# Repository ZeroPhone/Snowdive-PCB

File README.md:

# Snowdive PCBs

- `top_board_zero`: Snowdive top board for Pi Zero-compatible SBCs
- `bottom_board_palmtop`: Snowdive addon board that converts a top board into a palmtop

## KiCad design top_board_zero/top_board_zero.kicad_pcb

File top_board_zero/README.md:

# TOP-PIZERO Snowdive board v0

This board is confirmed to function standalone. It also is designed (but currently untested) to function connected to a bottom board, for instance, the BTM-PALMTOP.

## Requirements

This board works from a 5V/1.5A or 5V/3A input. If you want to get USB host mode out of the, you can use many of the generic "USB-C with data output and charger input" docks; connect the charger first, then plug the USB-C into the board.

You can still use the Pi Zero HDMI port for setup if required for OS setup.

You might benefit from a USB-UART adapter for debugging the system, though it's not required. A USB-UART adapter can be connected into the expansion header. Remember to check config.txt and cmdline.txt to make sure that UART console is enabled.

## Assembly

### FIXES REQUIRED FOR V0

- Remove resistor R6 (next to I2C GPIO expander U27 in the section `I2C GPIO a`),
- Add a ~51K resistor soldered to the VSYS side of C51 in `modem buck` section (can reuse the removed R6 for this)m
- Magnet wire the added resistor's other pin to pin 6 (EN) of U17 MIC2876, signal `EN_5V_BOOST`, section `5V boost`,
- Remove neopixels LED1 and LED2 at the top of the board (unless you've ensured that they're assembled correctly by JLCPCB, which has a likelihood of 50%).
- Desolder the TVS diode D5 in the `LTE modem` section if it's found out to be shorting the modem VBAT `+3V5` rail (possible if it was assembled incorrectly by JLCPCB, which has a likelihood of 50%).

### After-PCBA steps

- If assembled without a modem, solder on a modem as desired (not required)
- If assembled single-sided, solder on a SIM slot and an expansion header as desired (not required)
- Solder the Pi Zero on flush onto the board. Use a headers-less Pi Zero.
- Solder the Pi Zero USB testpoints to the solder points under the board using thin wires (i.e. magnet wire or stranded wire). Check for shorts to GND (in particular the microUSB shield pads) after soldering.

### After-assembly preparations

None.

## Bringup

### Testing under Linux

Make sure to run raspi-config to enable I2C, and that `i2c-dev` is added into `/etc/modules`.

### USB subsystem

**Before attempting to work with data on the USB-C port, slide the switch right next to it away from the USB-C port. This will disengage the hardware switch on the USB data pins.**

By default, USB from the Pi Zero is routed directly to the USB-C socket. This allows you to use the USB gadget mode (for networking/serial/storage over USB), as well as the BCM bootloader mode (entered upon boot without an SD card inserted).

If you want to enable the onboard USB hub (including the modem USB downlink and two of the downlinks exposed to a bottom board), you have to run these console commands:

```bash
i2cset -y 1 0x24 7 0xaf; i2cset -y 1 0x24 3 0xef
```

The `i2c-tools` package is a prerequisite for this - you can get it by using `sudo apt install i2c-tools`.

The USB-C socket will then get connected through a USB hub, instead of being connected directly.

Note: This command can also be executed when using a network connection over USB (i.e. USB-Ethernet), but do expect that you might need to open a new SSH session, as the old session might freeze.

*Next revision will join these pins into a single GPIO, so the command for V1 will change.*

### Modem

To power up the modem `+3V5` power rail, issue this command:

```bash
i2cset -y 1 0x25 7 0xef
```

The `i2c-tools` package is a prerequisite for this - you can get it by using `sudo apt install i2c-tools`.

## Notes

- I recommend ordering PCBA (PCB with assembly) for this board.
- The board is prepared for PCBA ordering, use the [kicad-jlcpcb-tools](https://github.com/Bouni/kicad-jlcpcb-tools/) plugin to generate output files.
- I recommend a stencil for assembling this board.

## Info

- Software: Kicad 9
- Version: 0
- PCB size: 111x80
- Layer count: 2
- Recommended thickness: 1.6mm

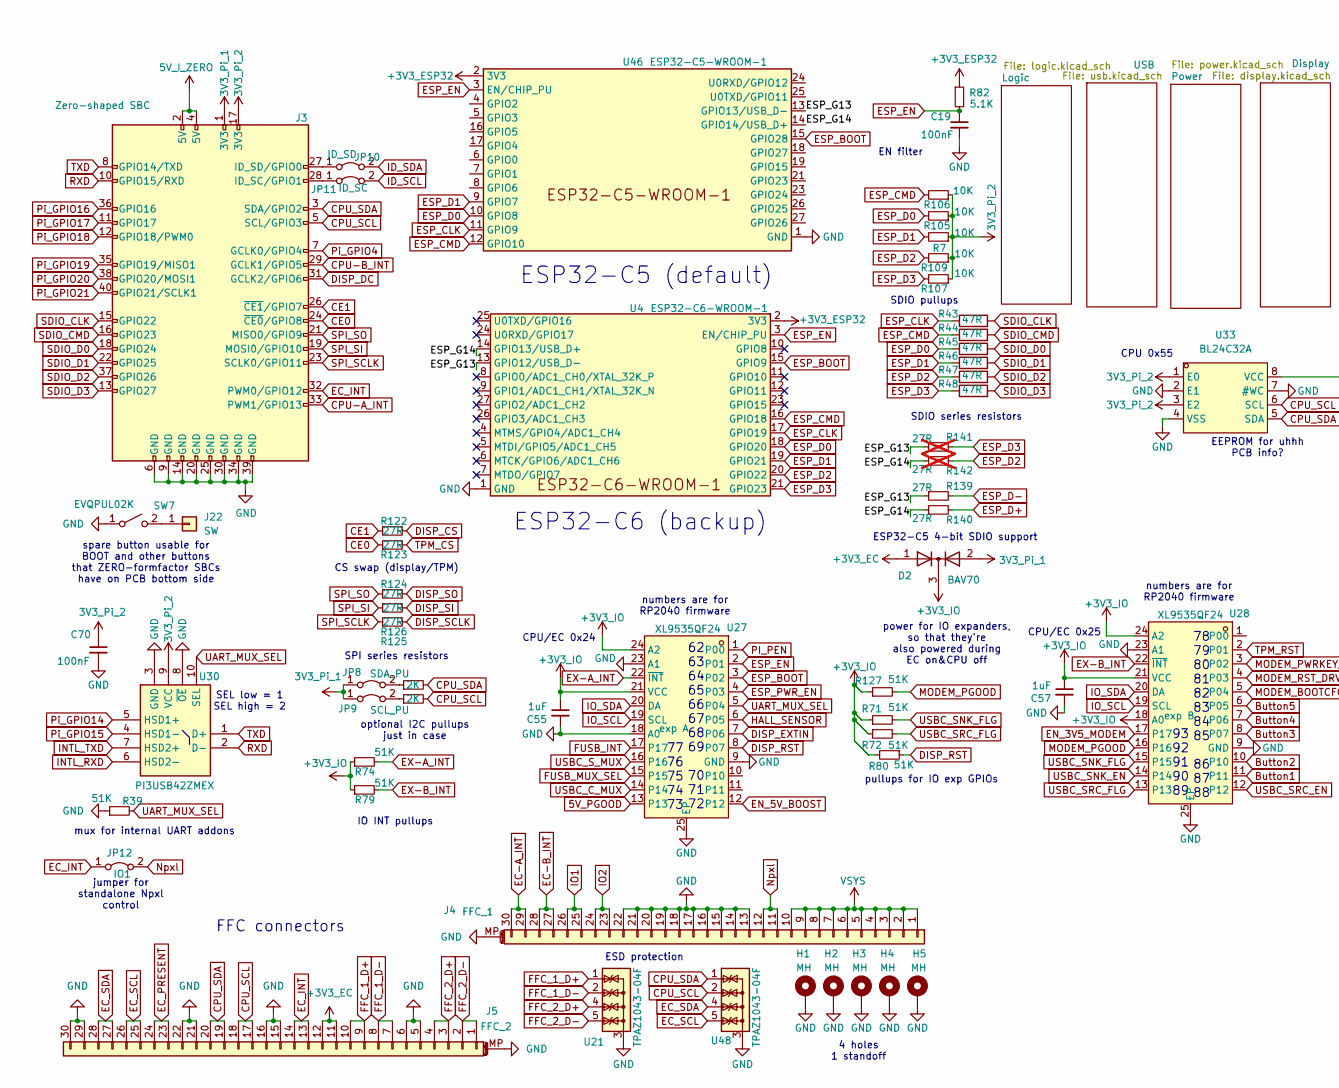
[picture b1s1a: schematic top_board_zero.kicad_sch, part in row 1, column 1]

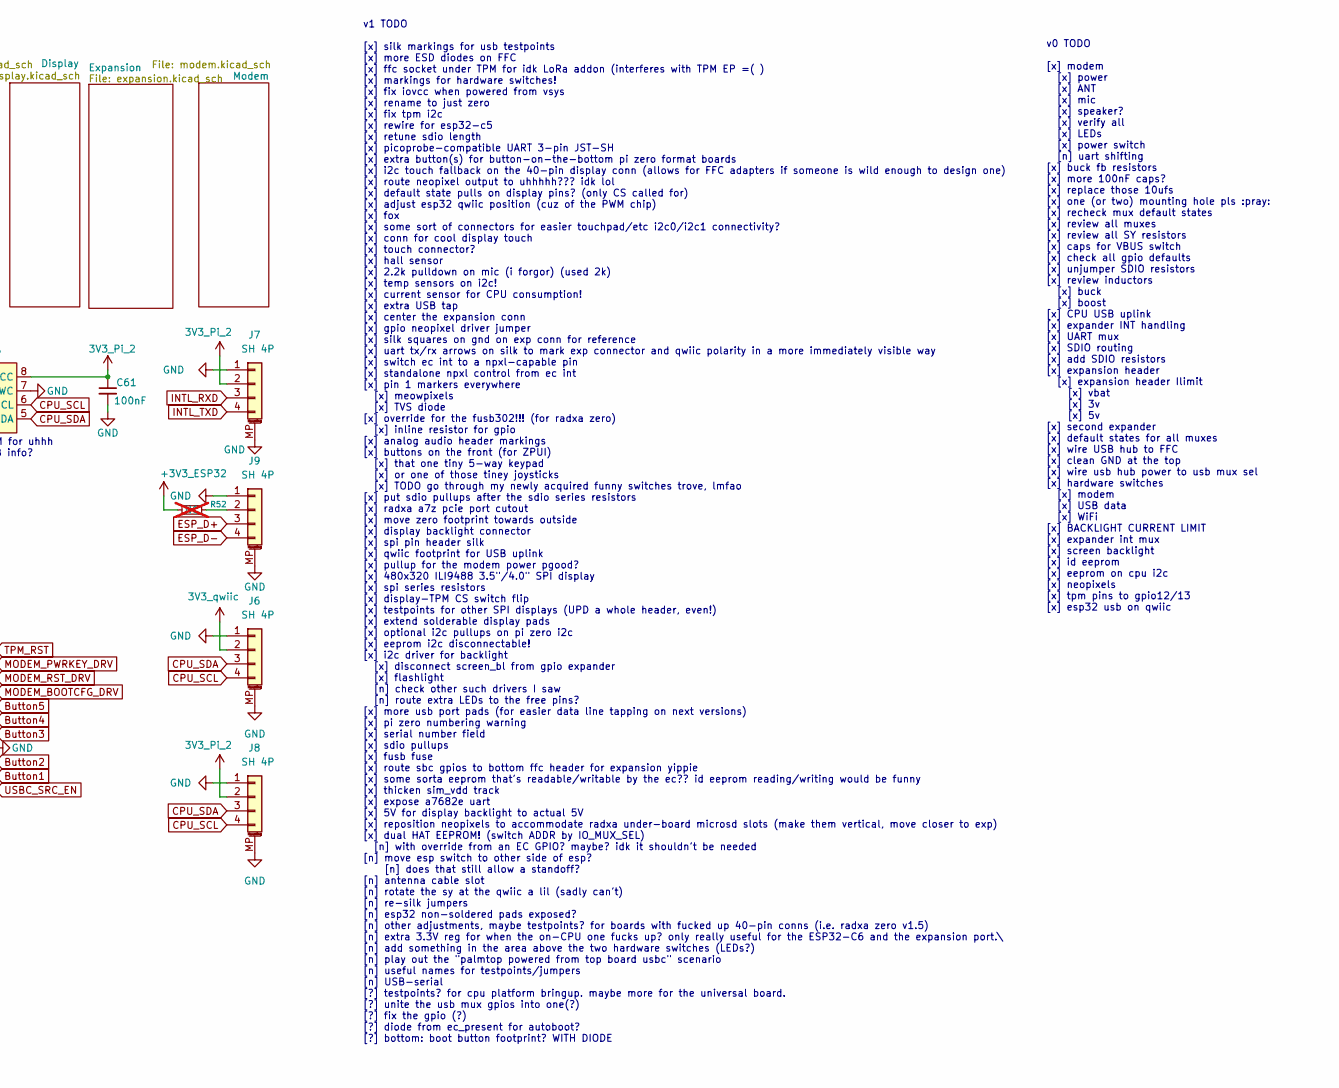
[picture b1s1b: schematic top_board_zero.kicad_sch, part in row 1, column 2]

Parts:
C19, C61, C70: 100nF; C_0402_1005Metric; LCSC Part C1525
C55, C57: 1uF; C_0402_1005Metric; LCSC Part C52923
D2: BAV70; SOT-23; LCSC Part C2501
H1, H2, H3, H4: MH; MountingHole_2.5mm_Pad
H5: MH; MountingHole_2.5mm_Pad-paste; LCSC Part C2916365
J3: Zero-shaped SBC; Raspberry_Pi_Zero_Socketed_THT_FaceDown_MountingHoles
J4: FFC_1; FPC-SMD_30P-P0.50_XF3M-3015-1B; LCSC Part C5700582
J5: FFC_2; FPC-SMD_30P-P0.50_XF3M-3015-1B; LCSC Part C5700582
J6, J7, J8, J9: SH 4P; JST_SH_SM04B-SRSS-TB_1x04-1MP_P1.00mm_Horizontal; LCSC Part C970137
J22: SW; PinHeader_1x01_P2.00mm_Vertical
JP8: SDA_PU; SolderJumper-2_smol_Open
JP9: SCL_PU; SolderJumper-2_smol_Open
JP10: ID_SD; SolderJumper-2_smol_Closed
JP11: ID_SC; SolderJumper-2_smol_Closed
JP12: IO1; SolderJumper-2_smol_Open
R7, R105, R106, R107, R109: 10K; R_0402_1005Metric; LCSC Part C25744
R39, R71, R72, R74, R79, R80, R127: 51K; R_0402_1005Metric; LCSC Part C25794
R43, R44, R45, R46, R47, R48: 47R; R_0402_1005Metric; LCSC Part C25118
R52: NC; R_0402_1005Metric; not fitted
R82: 5.1K; R_0402_1005Metric; LCSC Part C25905
R122, R123, R124, R125, R126, R139, R140: 27R; R_0402_1005Metric; LCSC Part C25105
R128, R129: 2K; R_0402_1005Metric; LCSC Part C4109
R141, R142: 27R; R_0402_1005Metric; LCSC Part C25105; not fitted
SW7: EVQPUL02K; Panasonic_EVQPUL_EVQPUC
U4: ESP32-C6-WROOM-1; ESP32-C6-WROOM-1_trimmed
U21, U48: TPAZ1043-04F; USON-10_2.5x1.0mm_P0.5mm
U27, U28: XL9535QF24; QFN-24-1EP_4x4mm_P0.5mm_EP2.5x2.5mm; LCSC Part C5444301
U30: PI3USB42ZMEX; QFN40P140X180X55-10N; Manufacturer_Part_Number FSUSB42UMX; Mouser Part Number 512-FSUSB42UMX
U33: BL24C32A; DFN-8-1EP_3x2mm_P0.5mm_EP1.3x1.5mm; LCSC Part C691878
U46: ESP32-C5-WROOM-1

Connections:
3V3_Pi_1: D2.2 (A), J3.1 (3V3), JP8.1 (A), JP9.1 (A); also elsewhere on the board
3V3_Pi_2: C61.1, C70.1, J3.17 (3V3), J7.2, J8.2, R7.1, R105.1, R106.1, R107.1, R109.1, U30.9 (VCC), U33.1 (E0), U33.3 (E2), U33.8 (VCC); also elsewhere on the board
3V3_qwiic: J6.2; also elsewhere on the board
5V_I_ZERO: J3.2 (5V), J3.4 (5V); also elsewhere on the board
5V_PGOOD: U27.13; also elsewhere on the board
+3V3_EC: D2.1 (A), J5.11, J5.12
+3V3_ESP32: R52.2, R82.1, U4.2 (3V3), U46.2 (3V3); also elsewhere on the board
+3V3_IO: C55.1, C57.1, D2.3 (K), R71.1, R72.1, R74.1, R79.1, R80.2, R127.1, U27.21 (VCC), U27.24 (A2), U28.18 (A0), U28.21 (VCC), U28.24 (A2); also elsewhere on the board
/ESP_G13: R139.1, R141.1, U4.13 (GPIO12/USB_D-), U46.13 (GPIO13/USB_D-)
/ESP_G14: R140.1, R142.1, U4.14 (GPIO13/USB_D+), U46.14 (GPIO14/USB_D+)
Button1: U28.11; also elsewhere on the board
Button2: U28.10; also elsewhere on the board
Button3: U28.8 (P07); also elsewhere on the board
Button4: U28.7 (P06); also elsewhere on the board
Button5: U28.6 (P05); also elsewhere on the board
CE0: J3.24 (~CE0/GPIO8), R123.1
CE1: J3.26 (~CE1/GPIO7), R122.1
CPU-A_INT: J3.33 (PWM1/GPIO13); also elsewhere on the board
CPU-B_INT: J3.29 (GCLK1/GPIO5); also elsewhere on the board
CPU_SCL: J3.5 (SCL/GPIO3), J5.17, J5.18, J6.4, J8.4, R129.2, U33.6 (SCL), U48.2 (IO2), U48.9 (NC); also elsewhere on the board
CPU_SDA: J3.3 (SDA/GPIO2), J5.19, J5.20, J6.3, J8.3, R128.2, U33.5 (SDA), U48.1 (IO1), U48.10 (NC); also elsewhere on the board
DISP_CS: R122.2; also elsewhere on the board
DISP_DC: J3.31 (GCLK2/GPIO6); also elsewhere on the board
DISP_EXTIN: U27.7 (P06); also elsewhere on the board
DISP_RST: R80.1, U27.8 (P07); also elsewhere on the board
DISP_SCLK: R126.2; also elsewhere on the board
DISP_SI: R125.2; also elsewhere on the board
DISP_SO: R124.2; also elsewhere on the board
EC-A_INT: J4.29, J4.30; also elsewhere on the board
EC-B_INT: J4.27, J4.28; also elsewhere on the board
EC_INT: J3.32 (PWM0/GPIO12), J5.13, J5.14, JP12.1 (A)
EC_PRESENT: J5.23, J5.24; also elsewhere on the board
EC_SCL: J5.25, J5.26, U48.5 (IO4), U48.6 (NC); also elsewhere on the board
EC_SDA: J5.27, J5.28, U48.4 (IO3), U48.7 (NC); also elsewhere on the board
EN_3V5_MODEM: U28.17; also elsewhere on the board
EN_5V_BOOST: U27.12; also elsewhere on the board
ESP_BOOT: U4.15 (GPIO9), U27.3 (P02), U46.15 (GPIO28)
ESP_CLK: R43.1, U4.17 (GPIO19), U46.11 (GPIO9); also elsewhere on the board
ESP_CMD: R44.1, R106.2, U4.16 (GPIO18), U46.12 (GPIO10); also elsewhere on the board
ESP_D0: R45.1, R105.2, U4.18 (GPIO20), U46.10 (GPIO8); also elsewhere on the board
ESP_D1: R7.2, R46.1, U4.19 (GPIO21), U46.9 (GPIO7); also elsewhere on the board
ESP_D2: R47.1, R109.2, R142.2, U4.20 (GPIO22); also elsewhere on the board
ESP_D3: R48.1, R107.2, R141.2, U4.21 (GPIO23); also elsewhere on the board
ESP_D+: J9.3, R140.2
ESP_D-: J9.4, R139.2
ESP_EN: C19.1, R82.2, U4.3 (EN/CHIP_PU), U27.2 (P01), U46.3 (EN/CHIP_PU)
ESP_PWR_EN: U27.4 (P03); also elsewhere on the board
EX-A_INT: R74.2, U27.22 (~INT); also elsewhere on the board
EX-B_INT: R79.2, U28.22 (~INT); also elsewhere on the board
FFC_1_D+: J5.9, J5.10, U21.1 (IO1), U21.10 (NC); also elsewhere on the board
FFC_1_D-: J5.7, J5.8, U21.2 (IO2), U21.9 (NC); also elsewhere on the board
FFC_2_D+: J5.3, J5.4, U21.4 (IO3), U21.7 (NC); also elsewhere on the board
FFC_2_D-: J5.1, J5.2, U21.5 (IO4), U21.6 (NC); also elsewhere on the board
FUSB_INT: U27.17; also elsewhere on the board
FUSB_MUX_SEL: U27.15; also elsewhere on the board
GND: C19.2, C55.2, C57.2, C61.2, C70.2, H1.1 (1_1), H2.1 (1_1), H3.1 (1_1), H4.1 (1_1), H5.1 (1_1), J3.6 (GND), J3.9 (GND), J3.14 (GND), J3.20 (GND), J3.25 (GND), J3.30 (GND), J3.34 (GND), J3.39 (GND), J4.13, J4.14, J4.15, J4.16, J4.17, J4.18, J4.19, J4.20, J4.21, J4.22, J4.MP (MountPin), J5.5, J5.6, J5.15, J5.16, J5.21, J5.22, J5.29, J5.30, J5.MP (MountPin), J6.1, J6.MP (MountPin), J7.1, J7.MP (MountPin), J8.1, J8.MP (MountPin), J9.1, J9.MP (MountPin), R39.1, SW7.1 (A), U4.1 (GND), U4.28 (GND), U4.29 (GND), U21.3 (G), U21.8 (G), U27.9 (GND), U27.18 (A0), U27.23 (A1), U27.25 (EP), U28.9 (GND), U28.23 (A1), U28.25 (EP), U30.3 (GND), U30.8 (~OE), U33.2 (E1), U33.4 (VSS), U33.7 (#WC), U46.1 (GND), U46.28 (GND), U46.29 (GND), U48.3 (G), U48.8 (G); also elsewhere on the board
HALL_SENSOR: U27.6 (P05); also elsewhere on the board
ID_SCL: JP11.2 (B); also elsewhere on the board
ID_SDA: JP10.2 (B); also elsewhere on the board
INTL_RXD: J7.3, U30.6 (HSD2-)
INTL_TXD: J7.4, U30.7 (HSD2+)
IO1: J4.25, J4.26; also elsewhere on the board
IO2: J4.23, J4.24; also elsewhere on the board
IO_SCL: U27.19 (SCL), U28.19 (SCL); also elsewhere on the board
IO_SDA: U27.20 (DA), U28.20 (DA); also elsewhere on the board
MODEM_BOOTCFG_DRV: U28.5 (P04); also elsewhere on the board
MODEM_PGOOD: R127.2, U28.16; also elsewhere on the board
MODEM_PWRKEY_DRV: U28.3 (P02); also elsewhere on the board
MODEM_RST_DRV: U28.4 (P03); also elsewhere on the board
unnamed: J3.28 (ID_SC/GPIO1), JP11.1 (A)
unnamed: J3.27 (ID_SD/GPIO0), JP10.1 (A)
unnamed: J9.2, R52.1
unnamed: J22.1 (Pin_1_1), SW7.2 (B)
unnamed: JP8.2 (B), R128.1
unnamed: JP9.2 (B), R129.1
Npxl: J4.11, J4.12, JP12.2 (B); also elsewhere on the board
PI_PEN: U27.1 (P00); also elsewhere on the board
Pi_GPIO4: J3.7 (GCLK0/GPIO4); also elsewhere on the board
Pi_GPIO14: U30.5 (HSD1+); also elsewhere on the board
Pi_GPIO15: U30.4 (HSD1-); also elsewhere on the board
Pi_GPIO16: J3.36 (GPIO16); also elsewhere on the board
Pi_GPIO17: J3.11 (GPIO17); also elsewhere on the board
Pi_GPIO18: J3.12 (GPIO18/PWM0); also elsewhere on the board
Pi_GPIO19: J3.35 (GPIO19/MISO1); also elsewhere on the board
Pi_GPIO20: J3.38 (GPIO20/MOSI1); also elsewhere on the board
Pi_GPIO21: J3.40 (GPIO21/SCLK1); also elsewhere on the board
RXD: J3.10 (GPIO15/RXD), U30.2 (D-)
SDIO_CLK: J3.15 (GPIO22), R43.2
SDIO_CMD: J3.16 (GPIO23), R44.2
SDIO_D0: J3.18 (GPIO24), R45.2
SDIO_D1: J3.22 (GPIO25), R46.2
SDIO_D2: J3.37 (GPIO26), R47.2
SDIO_D3: J3.13 (GPIO27), R48.2
SPI_SCLK: J3.23 (SCLK0/GPIO11), R126.1
SPI_SI: J3.19 (MOSI0/GPIO10), R125.1
SPI_SO: J3.21 (MISO0/GPIO9), R124.1
TPM_CS: R123.2; also elsewhere on the board
TPM_RST: U28.2 (P01); also elsewhere on the board
TXD: J3.8 (GPIO14/TXD), U30.1 (D+)
UART_MUX_SEL: R39.2, U27.5 (P04), U30.10 (SEL)
USBC_C_MUX: U27.14; also elsewhere on the board
USBC_SNK_EN: U28.14; also elsewhere on the board
USBC_SNK_FLG: R71.2, U28.15; also elsewhere on the board
USBC_SRC_EN: U28.12; also elsewhere on the board
USBC_SRC_FLG: R72.2, U28.13; also elsewhere on the board
USBC_S_MUX: U27.16; also elsewhere on the board
VSYS: J4.1, J4.2, J4.3, J4.4, J4.5, J4.6, J4.7, J4.8, J4.9, J4.10; also elsewhere on the board

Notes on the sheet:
93 92 91 90 89
SDIO pullups
CPU 0x55
optional I2C pullups just in case
SEL low = 1 SEL high = 2
EEPROM for uhhh PCB info?
v1 TODO [x] silk markings for usb testpoints [x] more ESD diodes on FFC [x] ffc socket under TPM for idk LoRa addon (interferes with TPM EP =( ) [x] markings for hardware switches! [x] fix iovcc when powered from vsys [x] rename to just zero [x] fix tpm i2c [x] rewire for esp32-c5 [x] retune sdio l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
spare button usable for BOOT and other buttons that ZERO-formfactor SBCs have on PCB bottom side
CS swap (display/TPM)
numbers are for RP2040 firmware
SDIO series resistors
ESP32-C5 4-bit SDIO support
CPU/EC 0x24
CPU/EC 0x25
pullups for IO exp GPIOs
mux for internal UART addons
78 79 80 81 82 83 84 85 86 87 88
ESP32-C6 (backup)
ESP32-C5 (default)
77 76 75 74 73
jumper for standalone Npxl control
FFC connectors
IO INT pullups
4 holes 1 standoff
EN filter
power for IO expanders, so that they're also powered during EC on&CPU off
SPI series resistors
v0 TODO [x] modem [x] power [x] ANT [x] mic [x] speaker? [x] verify all [x] LEDs [x] power switch [n] uart shifting [x] buck fb resistors [x] more 100nF caps? [x] replace those 10ufs [x] one (or two) mounting hole pls :pray: [x] recheck mux default states [x] review all muxes [x] review all SY resi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
ESD protection
62 63 64 65 66 67 68 69 70 71 72

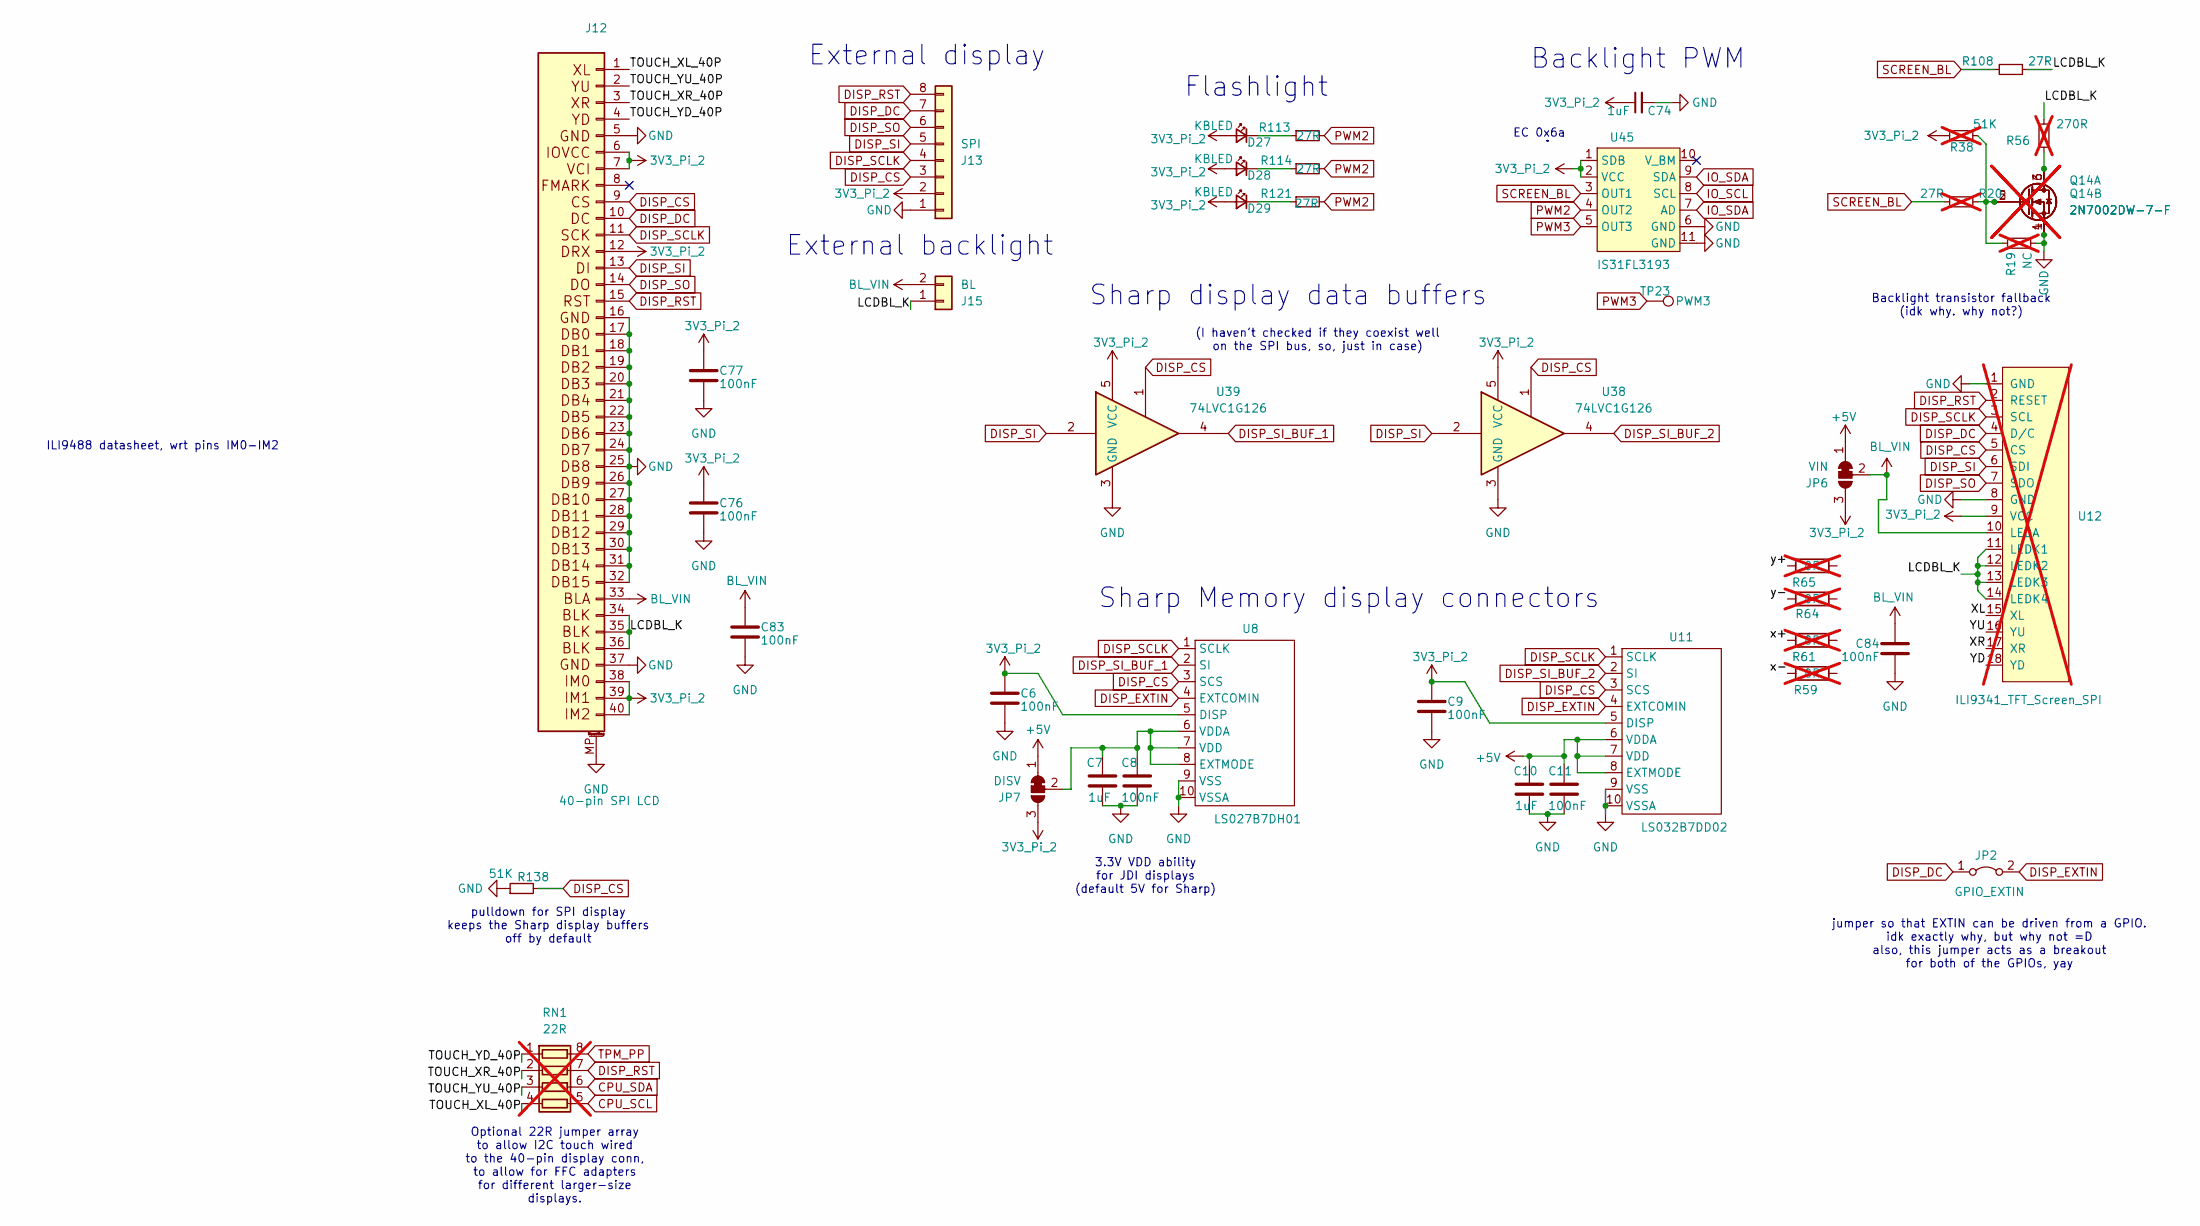
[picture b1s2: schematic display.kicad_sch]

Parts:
C6, C8, C9, C11, C76, C77, C83, C84: 100nF; C_0402_1005Metric; LCSC Part C1525
C7, C10, C74: 1uF; C_0402_1005Metric; LCSC Part C52923
D27, D28, D29: KBLED; LTW-010DCG
J12: 40-pin SPI LCD; ILI9488_3.5_4.0_DISPLAY; LCSC Part C2856837
J13: SPI; PinHeader_1x08_P2.54mm_Vertical
J15: BL; PinHeader_1x02_P2.54mm_Vertical
JP2: GPIO_EXTIN; SolderJumper-2_P1.3mm_Open_RoundedPad1.0x1.5mm
JP6: VIN; SolderJumper-3_P1.3mm_Bridged12_RoundedPad1.0x1.5mm
JP7: DISV; SolderJumper-3_P1.3mm_Bridged12_RoundedPad1.0x1.5mm
Q14: 2N7002DW-7-F; SOT-363_SC-70-6; LCSC Part C83571; not fitted
R19: NC; R_0402_1005Metric; not fitted
R20: 27R; R_0402_1005Metric; LCSC Part C25105; not fitted
R38: 51K; R_0402_1005Metric; LCSC Part C25794; not fitted
R56: 270R; R_0402_1005Metric; LCSC Part C25104; not fitted
R59, R61, R64, R65: 0R; R_0603_1608Metric_Jumper; not fitted
R108, R113, R114, R121: 27R; R_0402_1005Metric; LCSC Part C25105
R138: 51K; R_0402_1005Metric; LCSC Part C25794
RN1: 22R; R_Array_Concave_4x0402; not fitted
TP23: PWM3; TestPoint_Pad_1.5x1.5mm
U8: LS027B7DH01; HRS_FH34SRJ-10S-0.5SH(50); LCSC Part C5213731
U11: LS032B7DD02; HRS_FH34SRJ-10S-0.5SH(50); LCSC Part C5213731
U12: ILI9341_TFT_Screen_SPI; ILI9341_SCREEN_2.4INCH_SPI; not fitted
U38, U39: 74LVC1G126; SOT-23-5
U45: IS31FL3193; DFN-10-1EP_3x3mm_P0.5mm_EP1.7x2.5mm

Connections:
3V3_Pi_2: C6.1, C9.1, C74.1, C76.1, C77.1, D27.2 (A), D28.2 (A), D29.2 (A), J12.6, J12.7, J12.12, J12.38, J12.39, J12.40, J13.2, JP6.3 (B), JP7.3 (B), R38.1, U8.5 (DISP), U11.5 (DISP), U12.9 (VCC), U38.5 (VCC), U39.5 (VCC), U45.1 (SDB), U45.2 (VCC); also elsewhere on the board
+5V: C10.1, C11.1, JP6.1 (A), JP7.1 (A), U11.6 (VDDA), U11.7 (VDD), U11.8 (EXTMODE); also elsewhere on the board
/Display/LCDBL_K: J12.34, J12.35, J12.36, J15.1, R56.2, R108.1, U12.11 (LEDK1), U12.12 (LEDK2), U12.13 (LEDK3), U12.14 (LEDK4)
/Display/TOUCH_XL_40P: J12.1, RN1.4 (R4.1)
/Display/TOUCH_XR_40P: J12.3, RN1.2 (R2.1)
/Display/TOUCH_YD_40P: J12.4, RN1.1 (R1.1)
/Display/TOUCH_YU_40P: J12.2, RN1.3 (R3.1)
/Display/XL: U12.15 (XL)
/Display/XR: U12.17 (XR)
/Display/YD: U12.18 (YD)
/Display/YU: U12.16 (YU)
BL_VIN: C83.1, C84.1, J12.33, J15.2, JP6.2 (C), U12.10 (LEDA); also elsewhere on the board
CPU_SCL: RN1.5 (R4.2); also elsewhere on the board
CPU_SDA: RN1.6 (R3.2); also elsewhere on the board
DISP_CS: J12.9, J13.3, R138.2, U8.3 (SCS), U11.3 (SCS), U12.5 (CS), U38.1, U39.1; also elsewhere on the board
DISP_DC: J12.10, J13.7, JP2.1 (A), U12.4 (D/C); also elsewhere on the board
DISP_EXTIN: JP2.2 (B), U8.4 (EXTCOMIN), U11.4 (EXTCOMIN); also elsewhere on the board
DISP_RST: J12.15, J13.8, RN1.7 (R2.2), U12.2 (RESET); also elsewhere on the board
DISP_SCLK: J12.11, J13.4, U8.1 (SCLK), U11.1 (SCLK), U12.3 (SCL); also elsewhere on the board
DISP_SI: J12.13, J13.5, U12.6 (SDI), U38.2, U39.2; also elsewhere on the board
DISP_SI_BUF_1: U8.2 (SI), U39.4
DISP_SI_BUF_2: U11.2 (SI), U38.4
DISP_SO: J12.14, J13.6, U12.7 (SDO); also elsewhere on the board
GND: C6.2, C7.2, C8.2, C9.2, C10.2, C11.2, C74.2, C76.2, C77.2, C83.2, C84.2, J12.5, J12.16, J12.17, J12.18, J12.19, J12.20, J12.21, J12.22, J12.23, J12.24, J12.25, J12.26, J12.27, J12.28, J12.29, J12.30, J12.31, J12.32, J12.37, J12.MP (MountPin), J13.1, Q14.1 (S), Q14.4 (S), R19.1, R138.1, U8.9 (VSS), U8.10 (VSSA), U11.9 (VSS), U11.10 (VSSA), U12.1 (GND), U12.8 (GND), U38.3 (GND), U39.3 (GND), U45.6 (GND), U45.11 (GND); also elsewhere on the board
IO_SCL: U45.8 (SCL); also elsewhere on the board
IO_SDA: U45.7 (AD), U45.9 (SDA); also elsewhere on the board
unnamed: D27.1 (K), R113.1
unnamed: D28.1 (K), R114.1
unnamed: D29.1 (K), R121.1
unnamed: C7.1, C8.1, JP7.2 (C), U8.6 (VDDA), U8.7 (VDD), U8.8 (EXTMODE)
unnamed: Q14.3 (D), Q14.6 (D), R56.1
unnamed: Q14.2 (G), Q14.5 (G), R19.2, R20.2, R38.2
PWM2: R113.2, R114.2, R121.2, U45.4 (OUT2)
PWM3: TP23.1 (1_1), U45.5 (OUT3)
SCREEN_BL: R20.1, R108.2, U45.3 (OUT1)
TPM_PP: RN1.8 (R1.2); also elsewhere on the board

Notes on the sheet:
EC 0x6a
(I haven't checked if they coexist well on the SPI bus, so, just in case)
Optional 22R jumper array to allow I2C touch wired to the 40-pin display conn, to allow for FFC adapters for different larger-size displays.
Flashlight
Sharp Memory display connectors
ILI9488 datasheet, wrt pins IM0-IM2
3.3V VDD ability for JDI displays (default 5V for Sharp)
jumper so that EXTIN can be driven from a GPIO. idk exactly why, but why not =D also, this jumper acts as a breakout for both of the GPIOs, yay
Backlight transistor fallback (idk why. why not?)
External display
External backlight
nice
Backlight PWM
Sharp display data buffers
pulldown for SPI display keeps the Sharp display buffers off by default

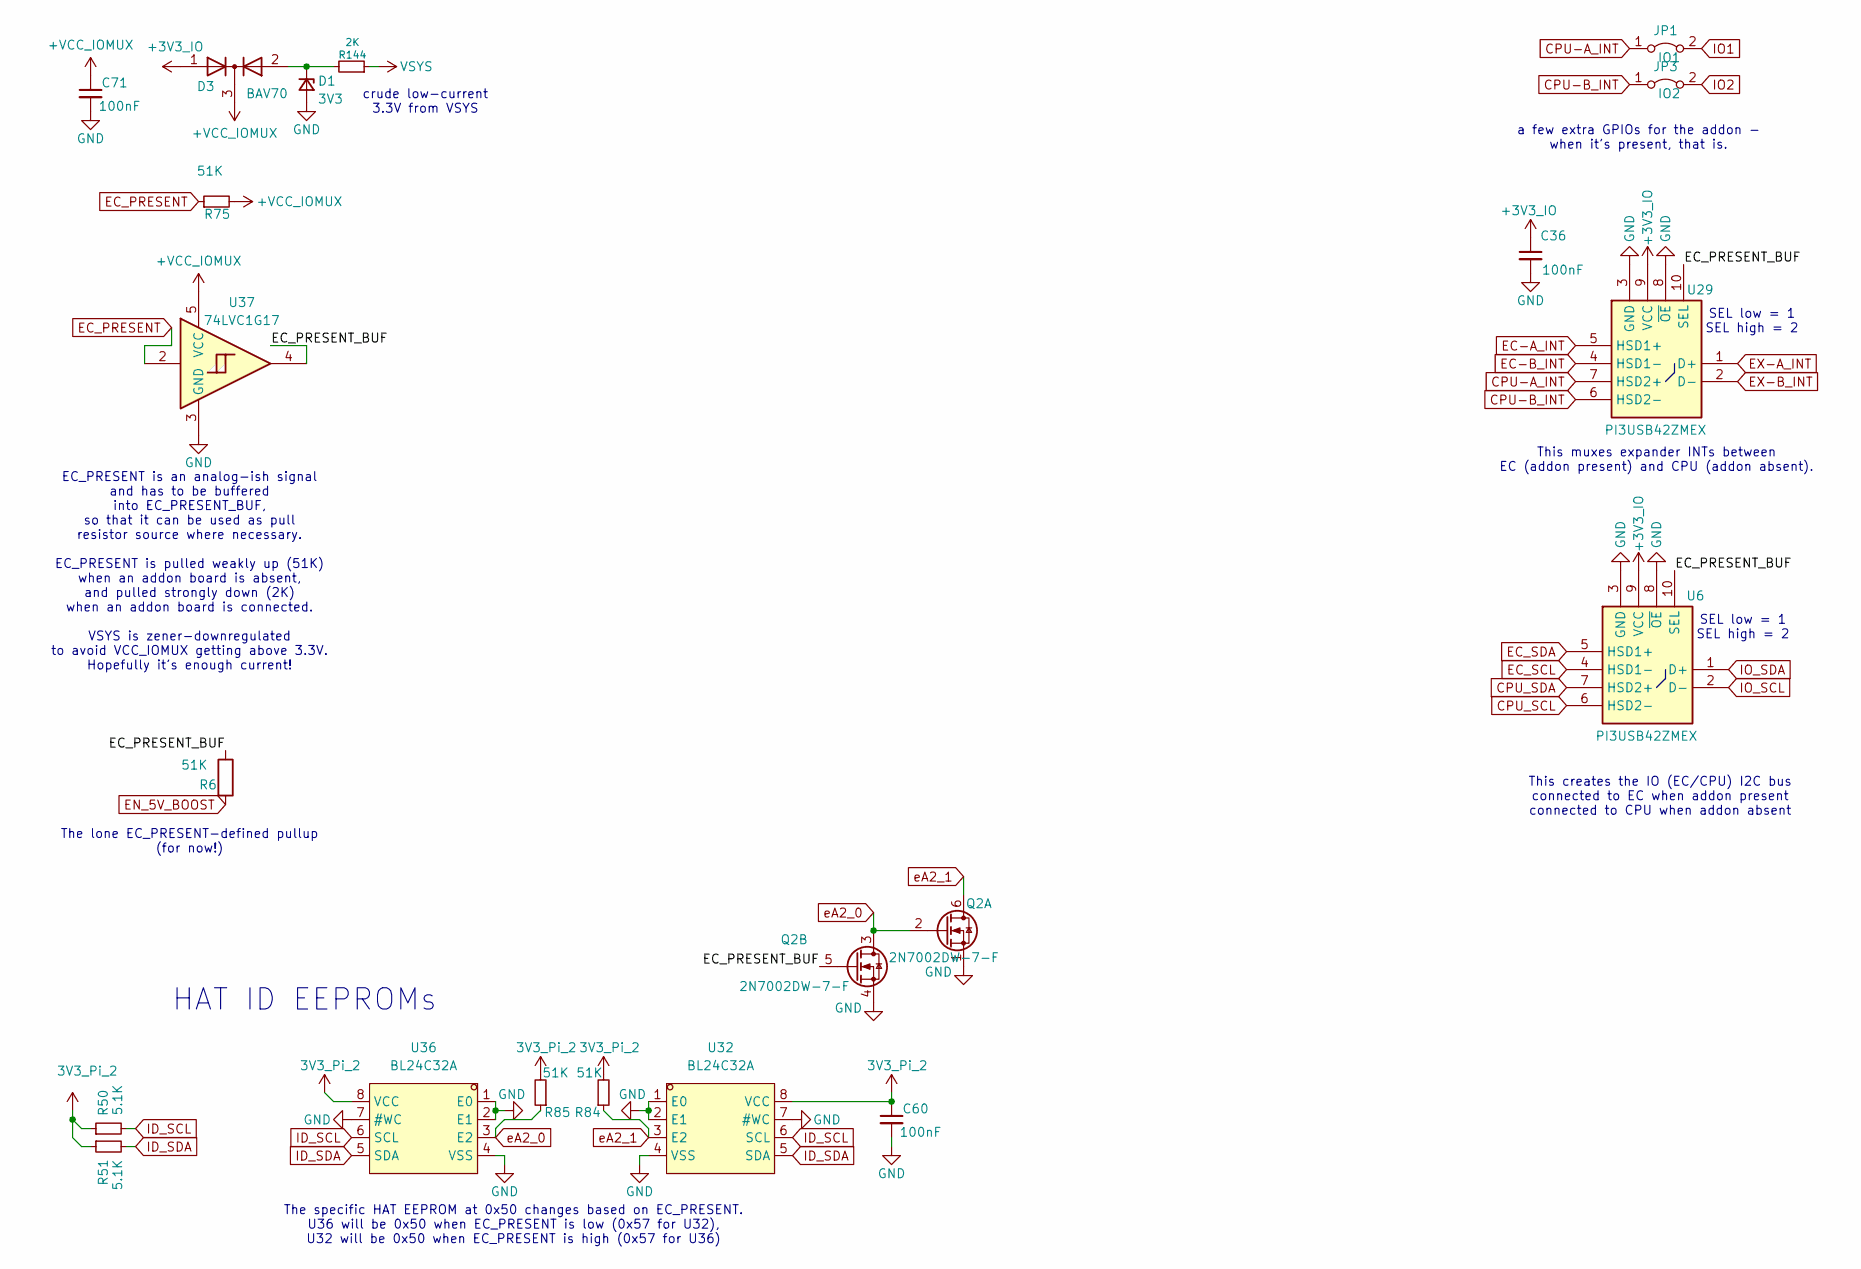
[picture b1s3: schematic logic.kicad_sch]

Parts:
C36, C60, C71: 100nF; C_0402_1005Metric; LCSC Part C1525
D1: 3V3; D_SOD-323; LCSC Part C75073
D3: BAV70; SOT-23; LCSC Part C2501
JP1: IO1; SolderJumper-2_P1.3mm_Bridged_RoundedPad1.0x1.5mm
JP3: IO2; SolderJumper-2_P1.3mm_Bridged_RoundedPad1.0x1.5mm
Q2: 2N7002DW-7-F; SOT-363_SC-70-6; LCSC Part C83571
R6, R75, R84, R85: 51K; R_0402_1005Metric; LCSC Part C25794
R50, R51: 5.1K; R_0402_1005Metric; LCSC Part C25905
R144: 2K; R_0402_1005Metric; LCSC Part C4109
U6, U29: PI3USB42ZMEX; QFN40P140X180X55-10N; Manufacturer_Part_Number FSUSB42UMX; Mouser Part Number 512-FSUSB42UMX
U32, U36: BL24C32A; DFN-8-1EP_3x2mm_P0.5mm_EP1.3x1.5mm; LCSC Part C691878
U37: 74LVC1G17; SOT-23-5

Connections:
3V3_Pi_2: C60.1, R50.1, R51.1, R84.2, R85.2, U32.8 (VCC), U36.8 (VCC); also elsewhere on the board
+3V3_IO: C36.1, D3.1 (A), U6.9 (VCC), U29.9 (VCC); also elsewhere on the board
+VCC_IOMUX: C71.1, D3.3 (K), R75.2, U37.5 (VCC)
/Logic/EC_PRESENT_BUF: Q2.5 (G), R6.1, U6.10 (SEL), U29.10 (SEL), U37.4
CPU-A_INT: JP1.1 (A), U29.7 (HSD2+); also elsewhere on the board
CPU-B_INT: JP3.1 (A), U29.6 (HSD2-); also elsewhere on the board
CPU_SCL: U6.6 (HSD2-); also elsewhere on the board
CPU_SDA: U6.7 (HSD2+); also elsewhere on the board
EC-A_INT: U29.5 (HSD1+); also elsewhere on the board
EC-B_INT: U29.4 (HSD1-); also elsewhere on the board
EC_PRESENT: R75.1, U37.2; also elsewhere on the board
EC_SCL: U6.4 (HSD1-); also elsewhere on the board
EC_SDA: U6.5 (HSD1+); also elsewhere on the board
EN_5V_BOOST: R6.2; also elsewhere on the board
EX-A_INT: U29.1 (D+); also elsewhere on the board
EX-B_INT: U29.2 (D-); also elsewhere on the board
GND: C36.2, C60.2, C71.2, D1.2 (A), Q2.1 (S), Q2.4 (S), U6.3 (GND), U6.8 (~OE), U29.3 (GND), U29.8 (~OE), U32.1 (E0), U32.2 (E1), U32.4 (VSS), U32.7 (#WC), U36.1 (E0), U36.2 (E1), U36.4 (VSS), U36.7 (#WC), U37.3 (GND); also elsewhere on the board
ID_SCL: R50.2, U32.6 (SCL), U36.6 (SCL); also elsewhere on the board
ID_SDA: R51.2, U32.5 (SDA), U36.5 (SDA); also elsewhere on the board
IO1: JP1.2 (B); also elsewhere on the board
IO2: JP3.2 (B); also elsewhere on the board
IO_SCL: U6.2 (D-); also elsewhere on the board
IO_SDA: U6.1 (D+); also elsewhere on the board
unnamed: D1.1 (K), D3.2 (A), R144.2
VSYS: R144.1; also elsewhere on the board
eA2_0: Q2.2 (G), Q2.3 (D), R85.1, U36.3 (E2)
eA2_1: Q2.6 (D), R84.1, U32.3 (E2)

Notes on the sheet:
SEL low = 1 SEL high = 2
HAT ID EEPROMs
This muxes expander INTs between EC (addon present) and CPU (addon absent).
a few extra GPIOs for the addon - when it's present, that is.
The lone EC_PRESENT-defined pullup (for now!)
EC_PRESENT is an analog-ish signal and has to be buffered into EC_PRESENT_BUF, so that it can be used as pull resistor source where necessary. EC_PRESENT is pulled weakly up (51K) when an addon board is absent, and pulled strongly down (2K) when an addon board is connected. VSYS is zener-downregula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
crude low-current 3.3V from VSYS
This creates the IO (EC/CPU) I2C bus connected to EC when addon present connected to CPU when addon absent
The specific HAT EEPROM at 0x50 changes based on EC_PRESENT. U36 will be 0x50 when EC_PRESENT is low (0x57 for U32), U32 will be 0x50 when EC_PRESENT is high (0x57 for U36)
